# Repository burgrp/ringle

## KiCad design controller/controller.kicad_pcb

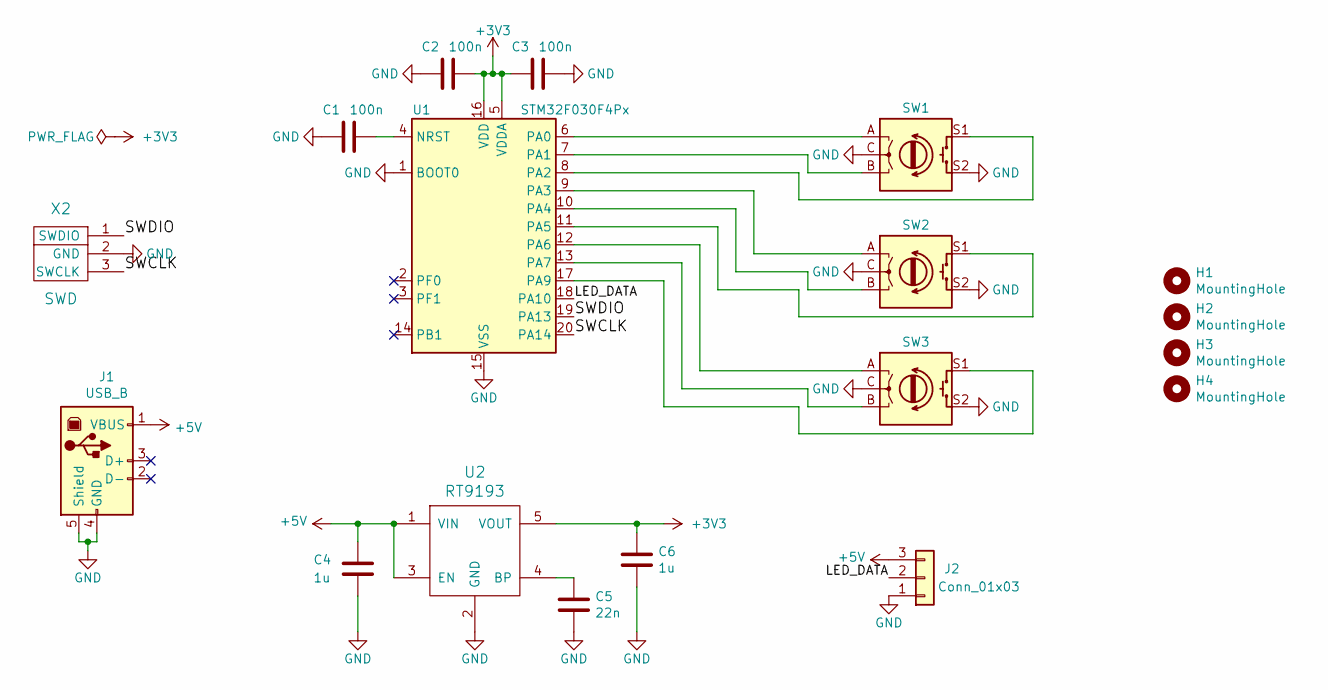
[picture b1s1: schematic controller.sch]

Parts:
C1, C2, C3: 100n; C_0805_2012Metric_Pad1.15x1.40mm_HandSolder
C4, C6: 1u; C_0805_2012Metric_Pad1.15x1.40mm_HandSolder
C5: 22n; C_0805_2012Metric_Pad1.15x1.40mm_HandSolder
H1, H2, H3, H4: MountingHole; MountingHole_3.7mm_Pad
J1: USB_B; USB_B_OST_USB-B1HSxx_Horizontal
J2: Conn_01x03; JST_XH_S3B-XH-A_1x03_P2.50mm_Horizontal
SW1, SW2, SW3: Rotary_Encoder_Switch; RotaryEncoder_Alps_EC12E-Switch_Vertical_H20mm
U1: STM32F030F4Px; SSOP-20_4.4x6.5mm_P0.65mm
U2: RT9193; SOT-23-5_HandSoldering
X2: SWD

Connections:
+3V3: C2.1, C3.2, C6.1, U1.5 (VDDA), U1.16 (VDD), U2.5 (VOUT)
+5V: C4.1, J1.1 (VBUS), J2.3, U2.1 (VIN), U2.3 (EN)
/LED_DATA: J2.2, U1.18 (PA10)
/SWCLK: U1.20 (PA14), X2.3 (SWCLK)
/SWDIO: U1.19 (PA13), X2.1 (SWDIO)
GND: C1.2, C2.2, C3.1, C4.2, C5.2, C6.2, J1.4 (GND), J1.5 (Shield), J2.1, SW1.C, SW1.S2, SW2.C, SW2.S2, SW3.C, SW3.S2, U1.1 (BOOT0), U1.15 (VSS), U2.2 (GND), X2.2 (GND)
unnamed: C1.1, U1.4 (NRST)
unnamed: C5.1, U2.4 (BP)
unnamed: SW1.A, U1.6 (PA0)
unnamed: SW1.B, U1.7 (PA1)
unnamed: SW1.S1, U1.8 (PA2)
unnamed: SW2.A, U1.9 (PA3)
unnamed: SW2.B, U1.10 (PA4)
unnamed: SW2.S1, U1.11 (PA5)
unnamed: SW3.A, U1.12 (PA6)
unnamed: SW3.B, U1.13 (PA7)
unnamed: SW3.S1, U1.17 (PA9)

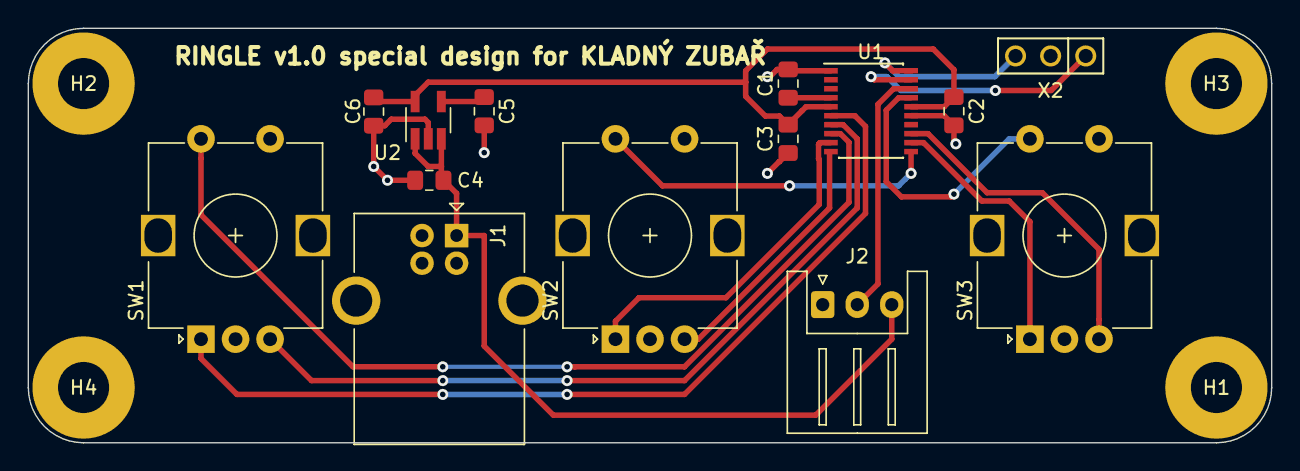
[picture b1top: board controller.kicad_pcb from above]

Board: 2 copper layers, 90.0 x 30.0 mm, 18 parts (0 on the bottom side), 17 nets.
